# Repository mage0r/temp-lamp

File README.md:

Temp Lamp
=============
The "Temp Lamp" circuit is a battery powered simple temperature sensor.  It adjusts the colour of the LED depending on the current ambient temperature.

CREDITS
------------

This project was designed by [John Spencer](https://github.com/mage0r)

Made at hackmelbourne.org!

SPECIAL THANKS
------------

To the HackMelbourne (CCHS, http://hackmelbourne.org) community of Melbourne, Australia.

To all other open-source developers whose countless hours supported every other aspect of this design.

DISTRIBUTION
------------
The specific terms of distribution of this project are governed by the
license referenced below. Please contact the copyright owner if you wish to modify the board for distribution. Please utilize this design for personal or research projects. Please acknowledge all contributors.

LICENSE
-------
Licensed under the TAPR Open Hardware License (www.tapr.org/OHL).
The "license" sub-folder also contains a copy of this license in plain text format.

Copyright John Spencer 2016

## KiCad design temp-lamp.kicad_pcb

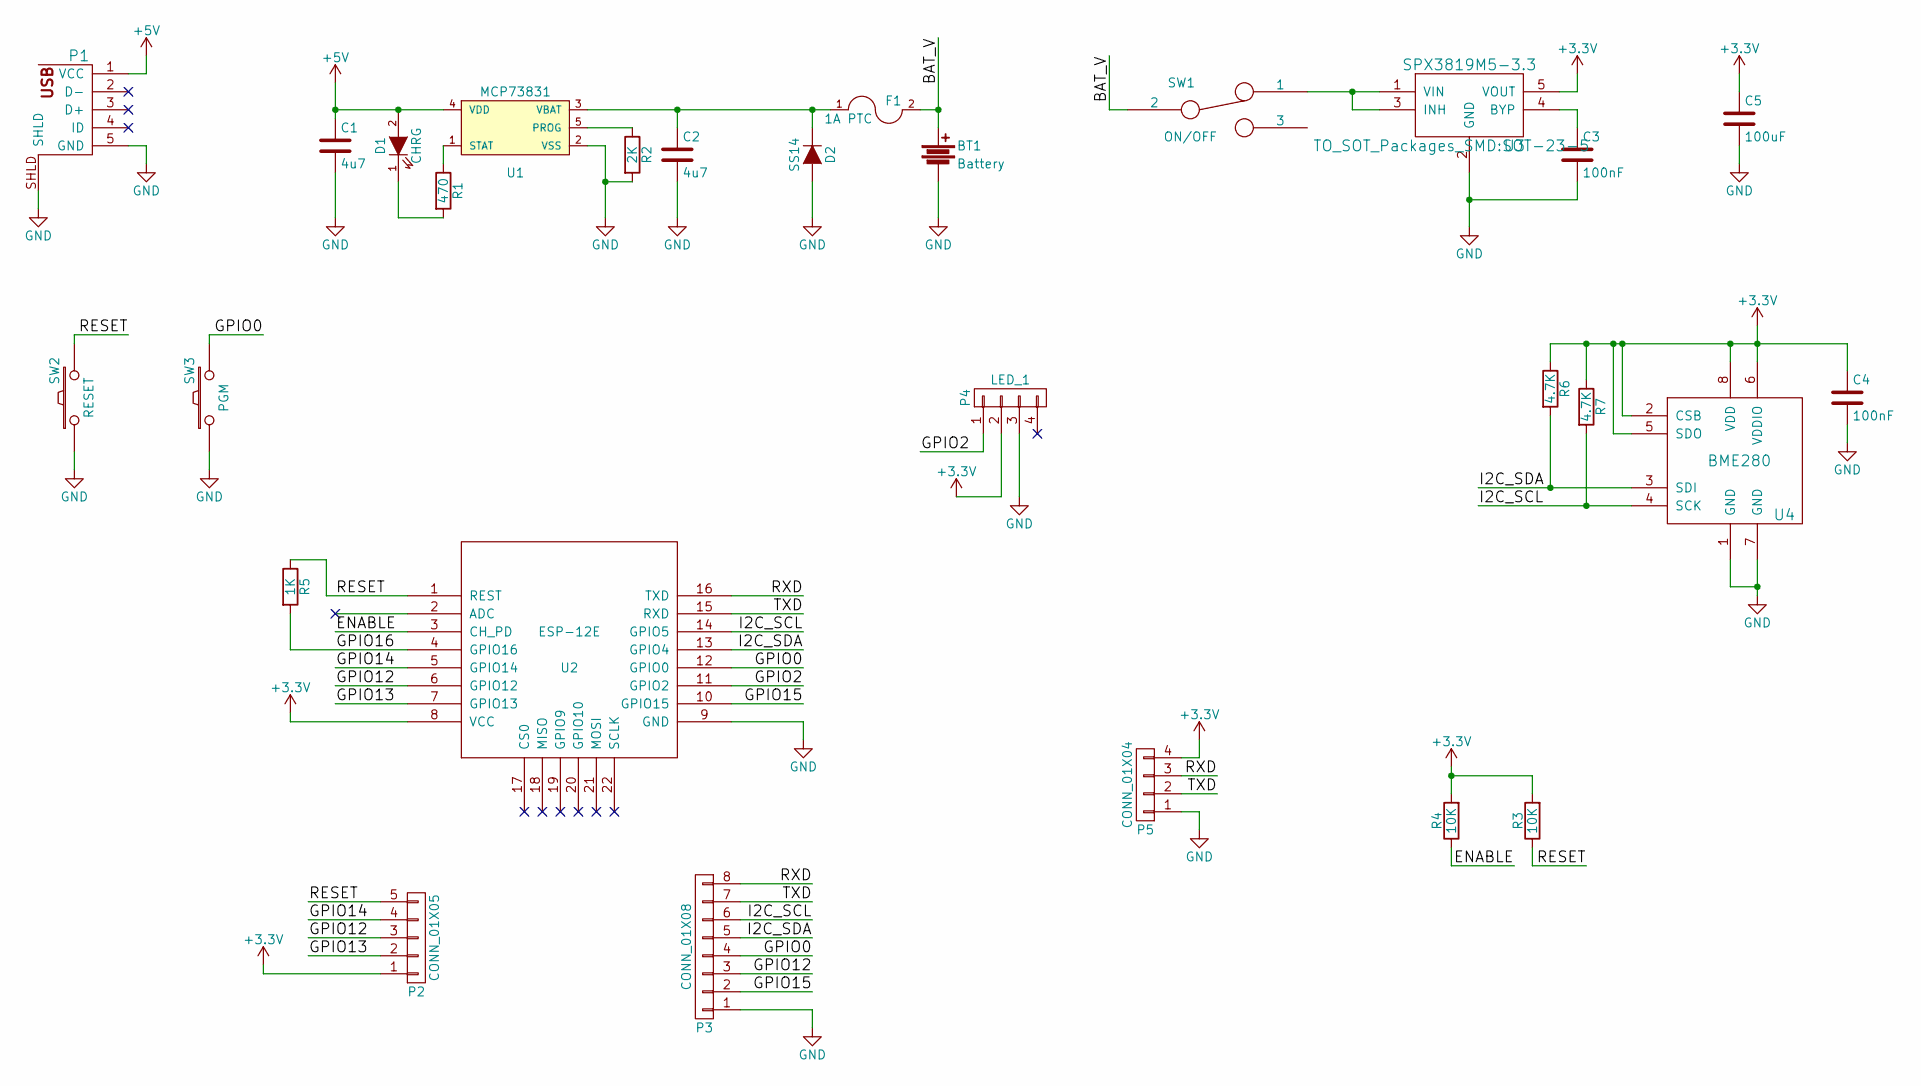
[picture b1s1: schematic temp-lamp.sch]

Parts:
BT1: Battery; CR123_Holder
C1, C2: 4u7; C_0603_HandSoldering
C3, C4: 100nF; C_0603_HandSoldering
C5: 100uF; C_1206_HandSoldering
D1: CHRG; LED_0603
D2: SS14; DIODE_SMA
F1: 1A PTC; C_1210_HandSoldering
P1: USB_5PIN_SHELL; USB-MICRO-5pin_PTHMOUNT
P2: CONN_01X05; SMD_1x05_Pitch2.54mm
P3: CONN_01X08; SMD_1x08_Pitch2.54mm
P4: LED_1; LED_8MM_APA-106
P5: CONN_01X04; Pin_Header_Straight_1x04_Pitch2.54mm
R1: 470; R_0603_HandSoldering
R2: 2K; R_0603_HandSoldering
R3, R4: 10K; R_0603_HandSoldering
R5: 1K; R_0603_HandSoldering
R6, R7: 4.7K; R_0603_HandSoldering
SW1: ON/OFF; SS12D00
SW2: RESET; Pin_Header_Straight_1x02_Pitch2.54mm
SW3: PGM; Pin_Header_Straight_1x02_Pitch2.54mm
U1: MCP73831; SOT-23-5
U2: ESP-12E
U3: SPX3819M5-3.3; SOT-23-5
U4: BME280

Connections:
+3V3: C4.1, C5.1, P2.1, P4.2, P5.4, R3.2, R4.2, R6.1, R7.1, U2.8 (VCC), U3.5 (VOUT), U4.2 (CSB), U4.5 (SDO), U4.6 (VDDIO), U4.8 (VDD)
+5V: C1.1, D1.2 (A), P1.1 (VCC), U1.4 (VDD)
/BAT_V: BT1.1, F1.2, SW1.2
/ENABLE: R4.1, U2.3 (CH_PD)
/GPIO0: P3.4, SW3.2, U2.12 (GPIO0)
/GPIO2: P4.1, U2.11 (GPIO2)
/GPIO12: P2.3, P3.3, U2.6 (GPIO12)
/GPIO13: P2.2, U2.7 (GPIO13)
/GPIO14: P2.4, U2.5 (GPIO14)
/GPIO15: P3.2, U2.10 (GPIO15)
/GPIO16: R5.2, U2.4 (GPIO16)
/I2C_SCL: P3.6, R7.2, U2.14 (GPIO5), U4.4 (SCK)
/I2C_SDA: P3.5, R6.2, U2.13 (GPIO4), U4.3 (SDI)
/RESET: P2.5, R3.1, R5.1, SW2.2, U2.1 (REST)
/RXD: P3.8, P5.3, U2.16 (TXD)
/TXD: P3.7, P5.2, U2.15 (RXD)
GND: BT1.2, C1.2, C2.2, C3.2, C4.2, C5.2, D2.1 (A), P1.5 (GND), P1.SHLD, P3.1, P4.3, P5.1, R2.2, SW2.1, SW3.1, U1.2 (VSS), U2.9 (GND), U3.2 (GND), U4.1 (GND), U4.7 (GND)
unnamed: C2.1, D2.2 (K), F1.1, U1.3 (VBAT)
unnamed: C3.1, U3.4 (BYP)
unnamed: D1.1 (K), R1.2
unnamed: R1.1, U1.1 (STAT)
unnamed: R2.1, U1.5 (PROG)
unnamed: SW1.1, U3.1 (VIN), U3.3 (INH)

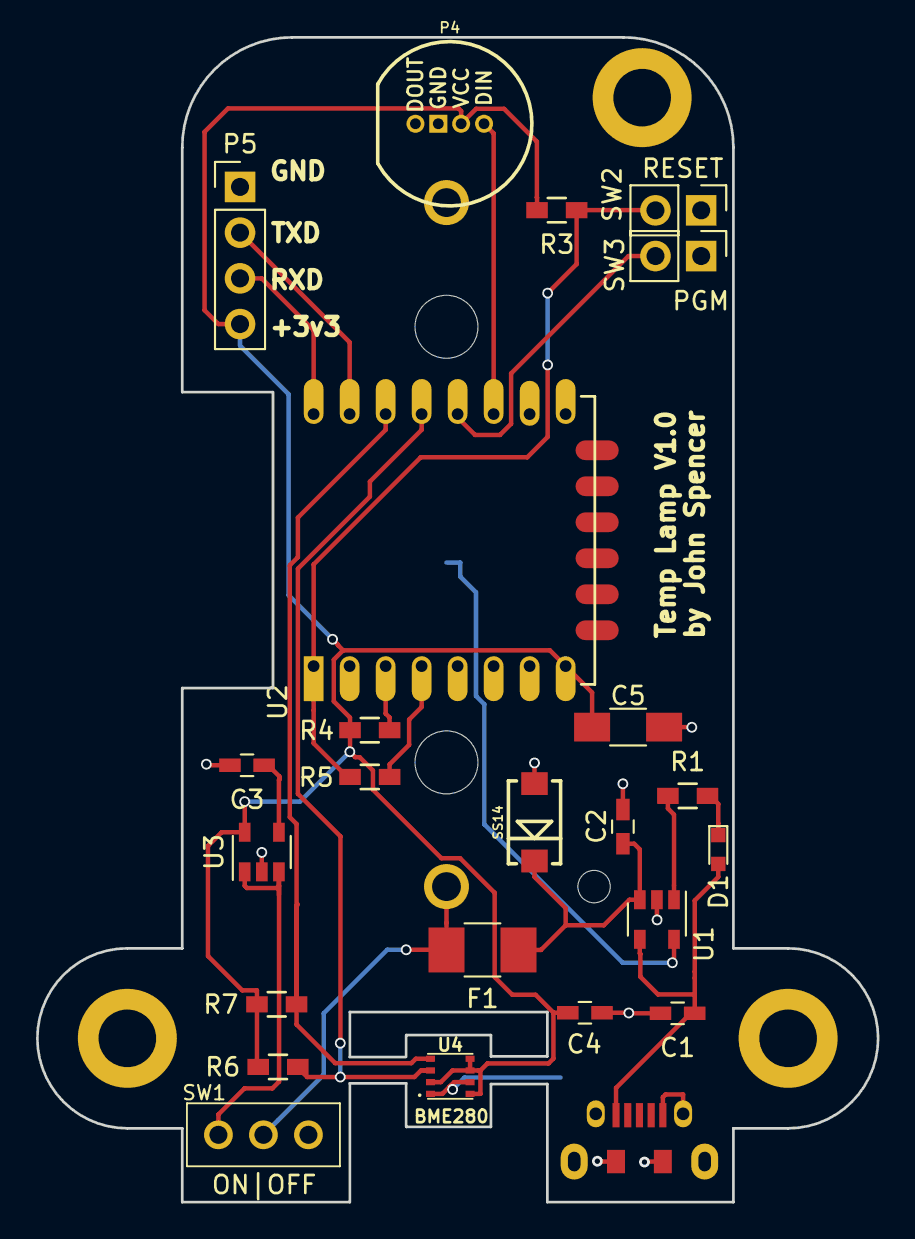
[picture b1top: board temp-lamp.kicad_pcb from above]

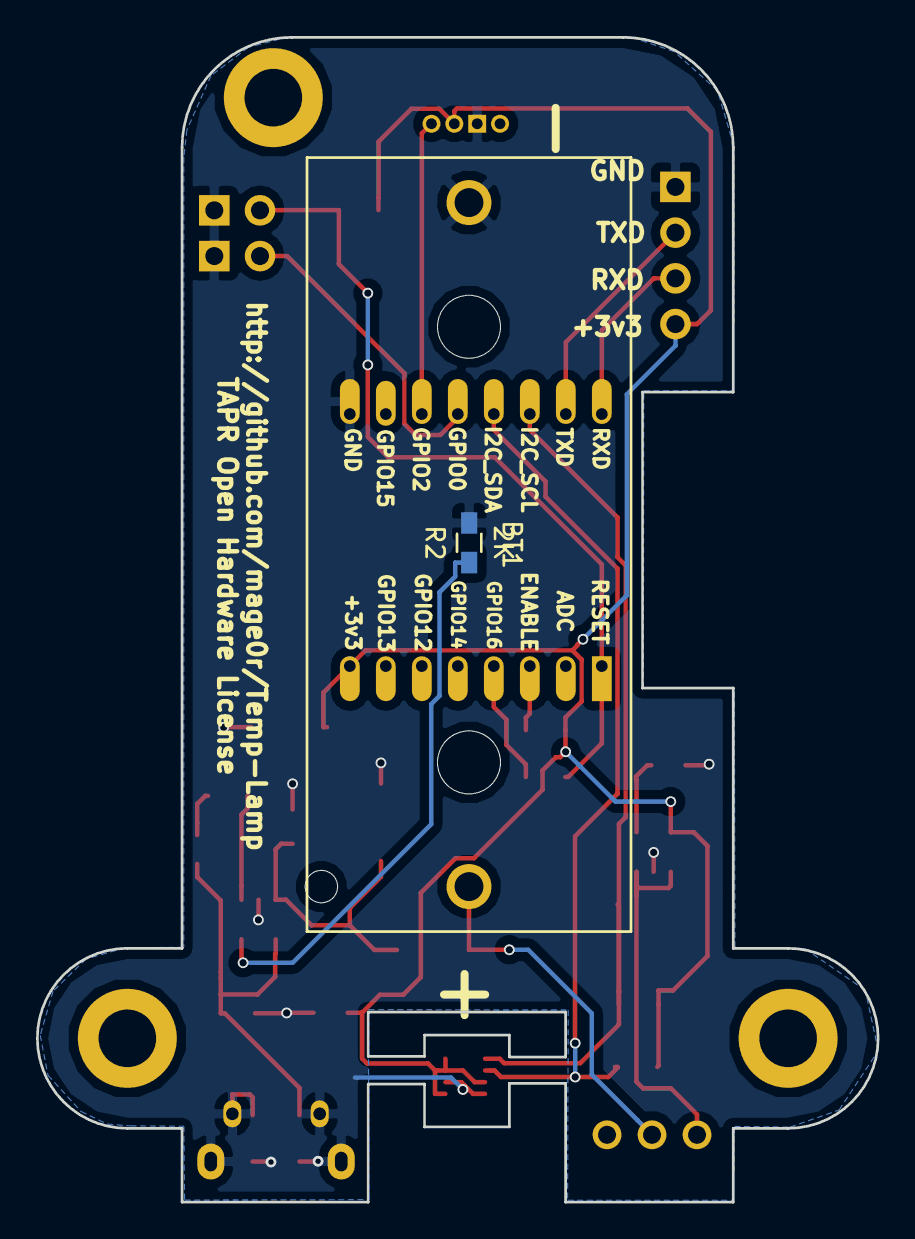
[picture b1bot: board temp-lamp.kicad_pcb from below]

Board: 2 copper layers, 46.7 x 64.7 mm, 29 parts (2 on the bottom side), 19 nets.

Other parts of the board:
M2, M3: M3; MountingHole_3.2mm_M3_ISO14580_Pad
MH1: M3; MountingHole_3.2mm_M3_ISO14580_Pad

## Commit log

2017-01-19 :circus_tent: Added .gitattributes & .gitignore files
2017-01-26 Rename of project
2017-01-26 Some weirdness with submodules.
2017-01-26 Added Readme
2017-01-26 Shuffled some capacitors around
    to make @projectgus happy...
2017-02-20 Updated pcb.
